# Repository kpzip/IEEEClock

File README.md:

# IEEEClock
Back to the future style clock

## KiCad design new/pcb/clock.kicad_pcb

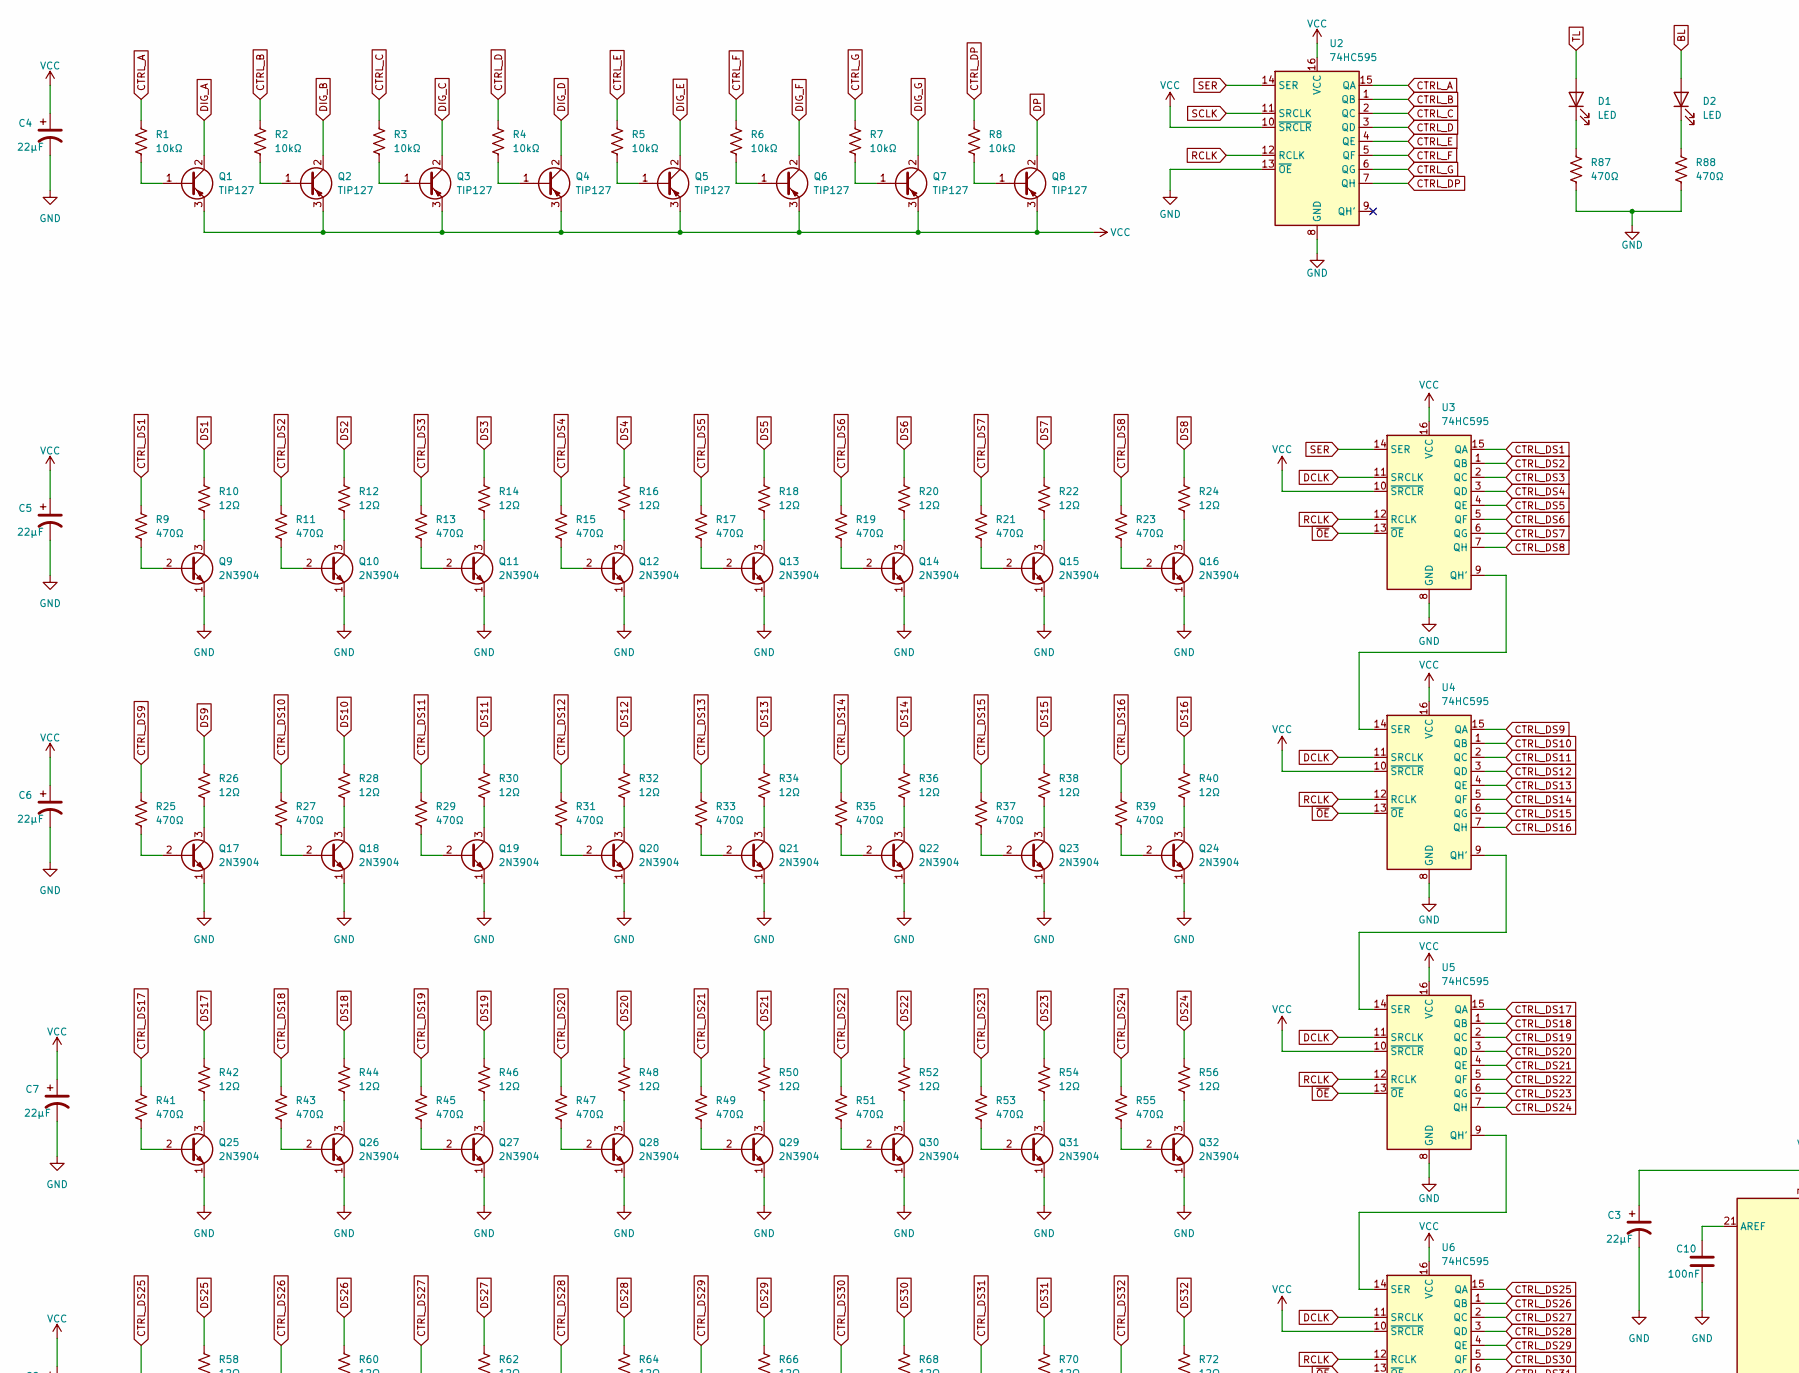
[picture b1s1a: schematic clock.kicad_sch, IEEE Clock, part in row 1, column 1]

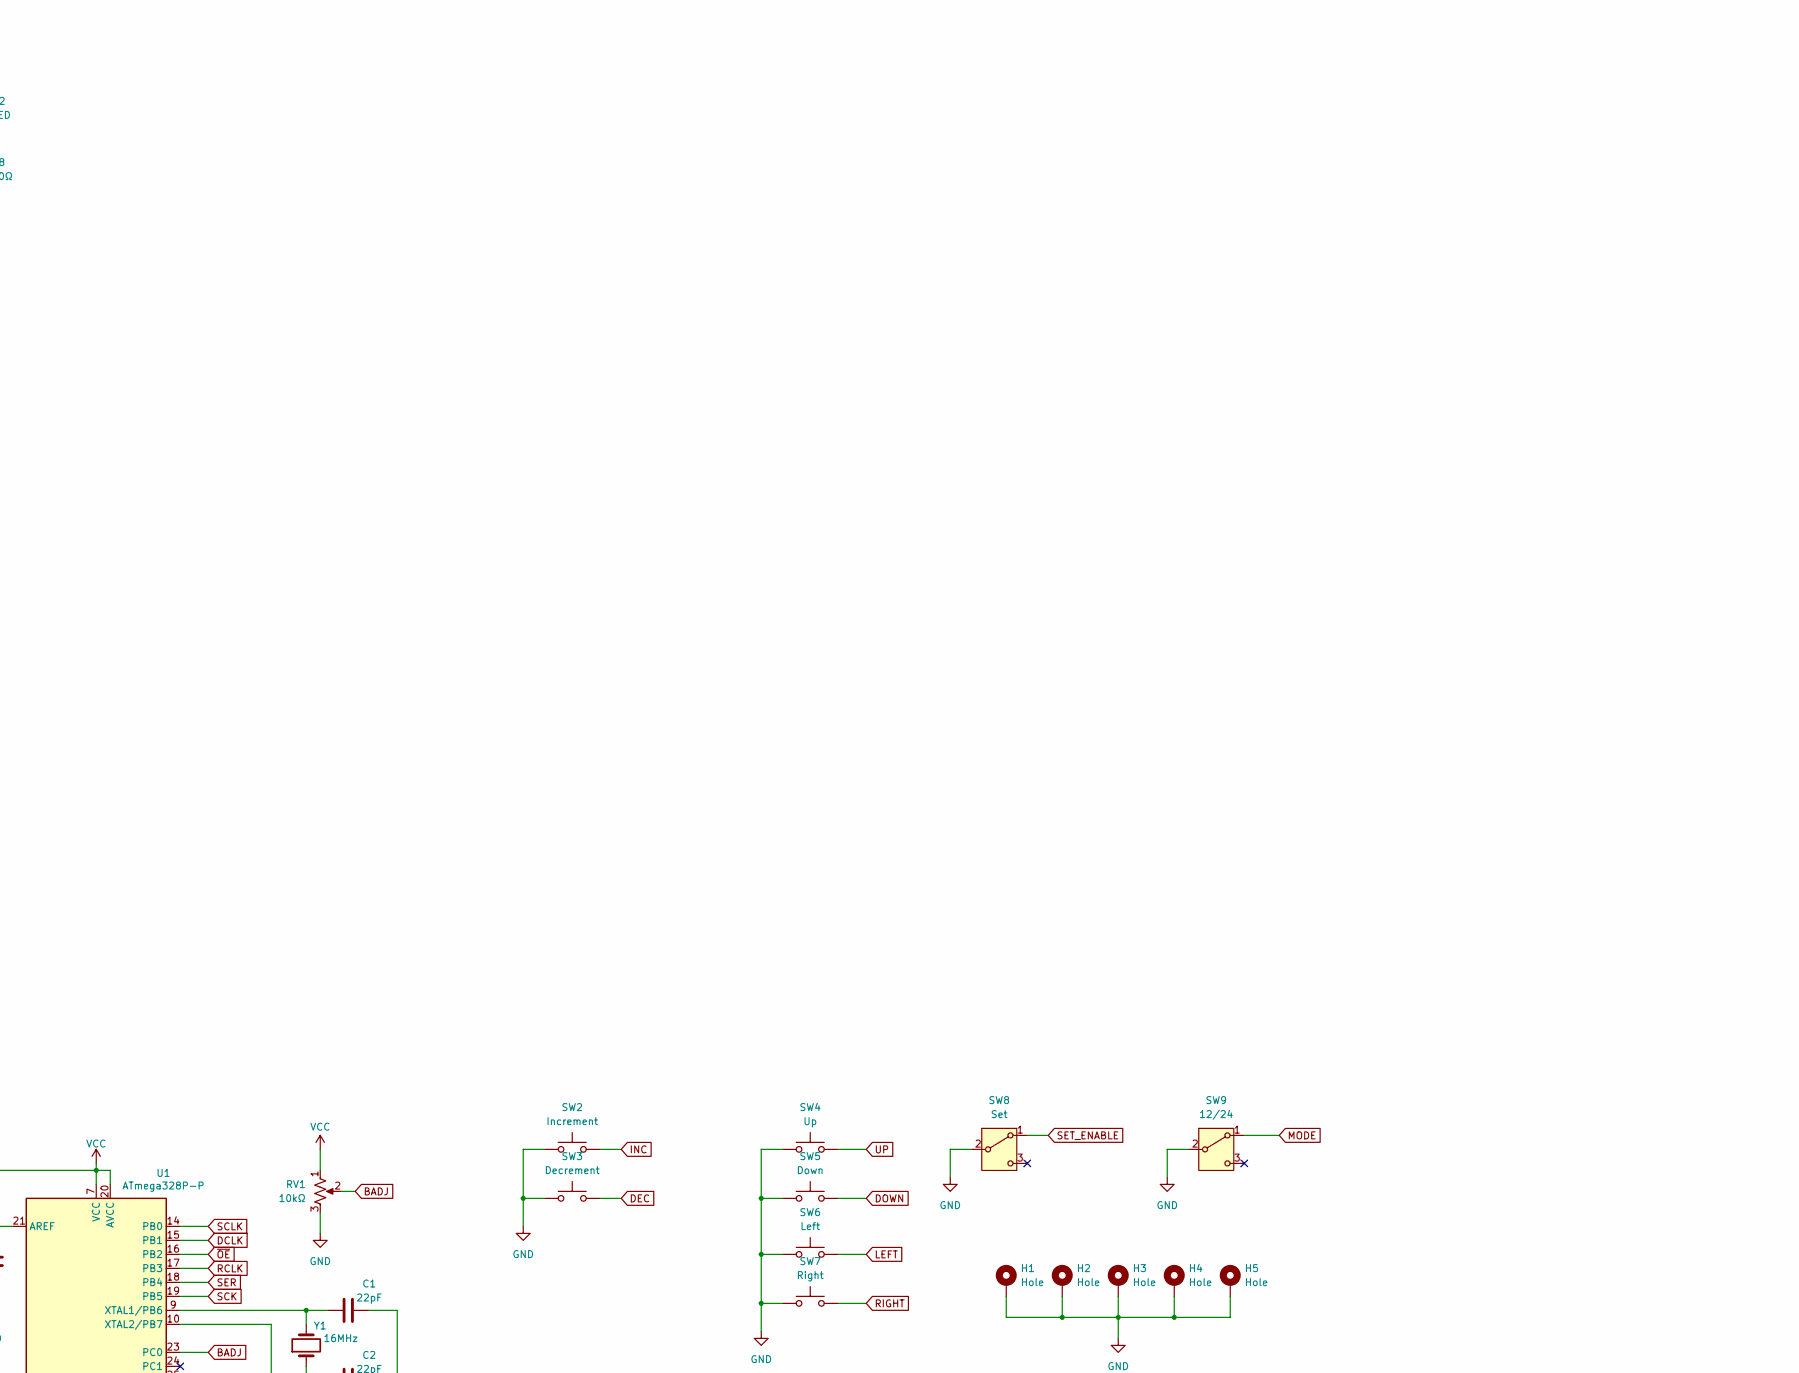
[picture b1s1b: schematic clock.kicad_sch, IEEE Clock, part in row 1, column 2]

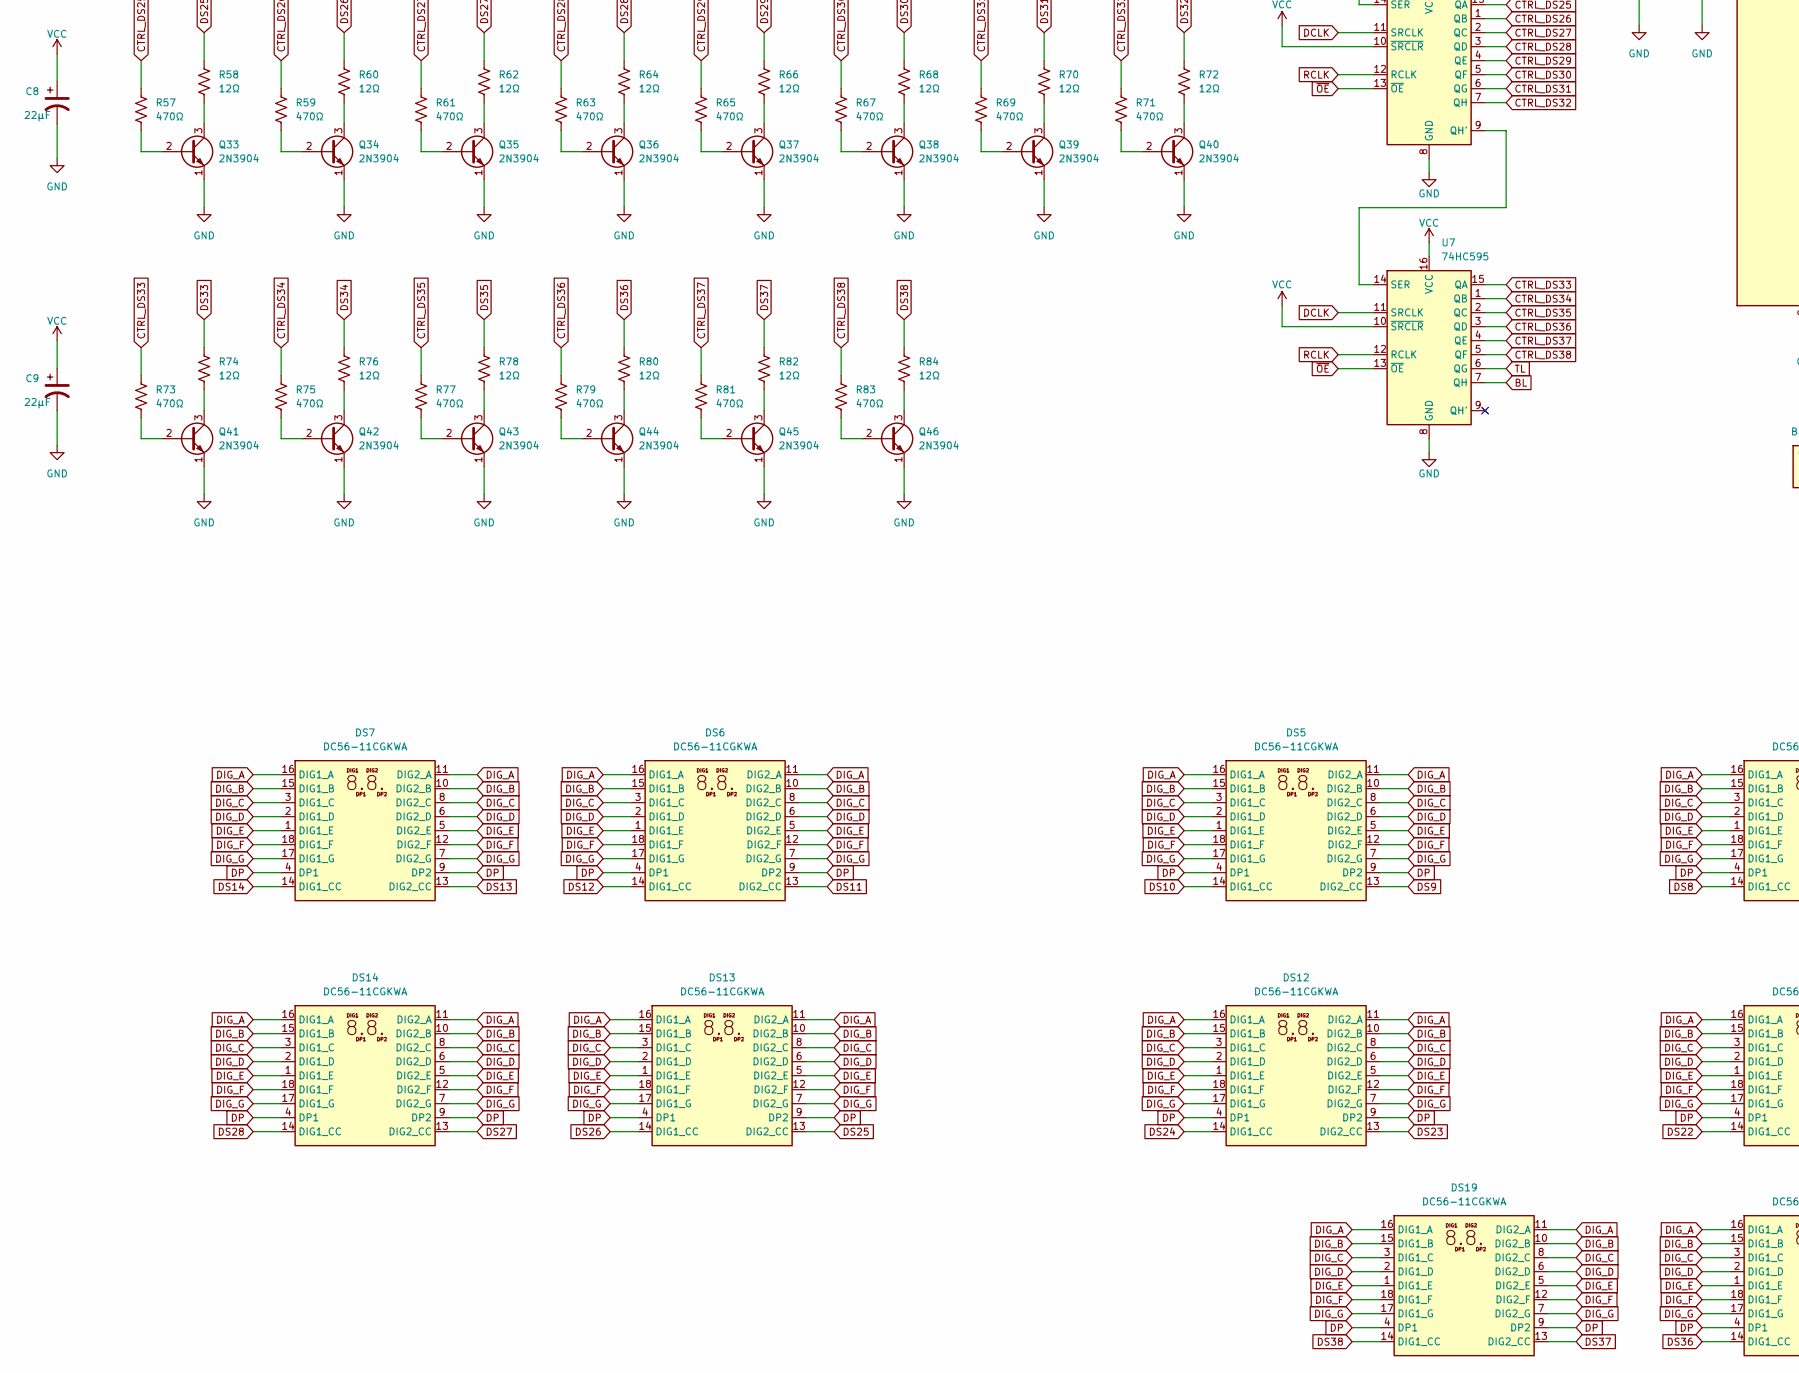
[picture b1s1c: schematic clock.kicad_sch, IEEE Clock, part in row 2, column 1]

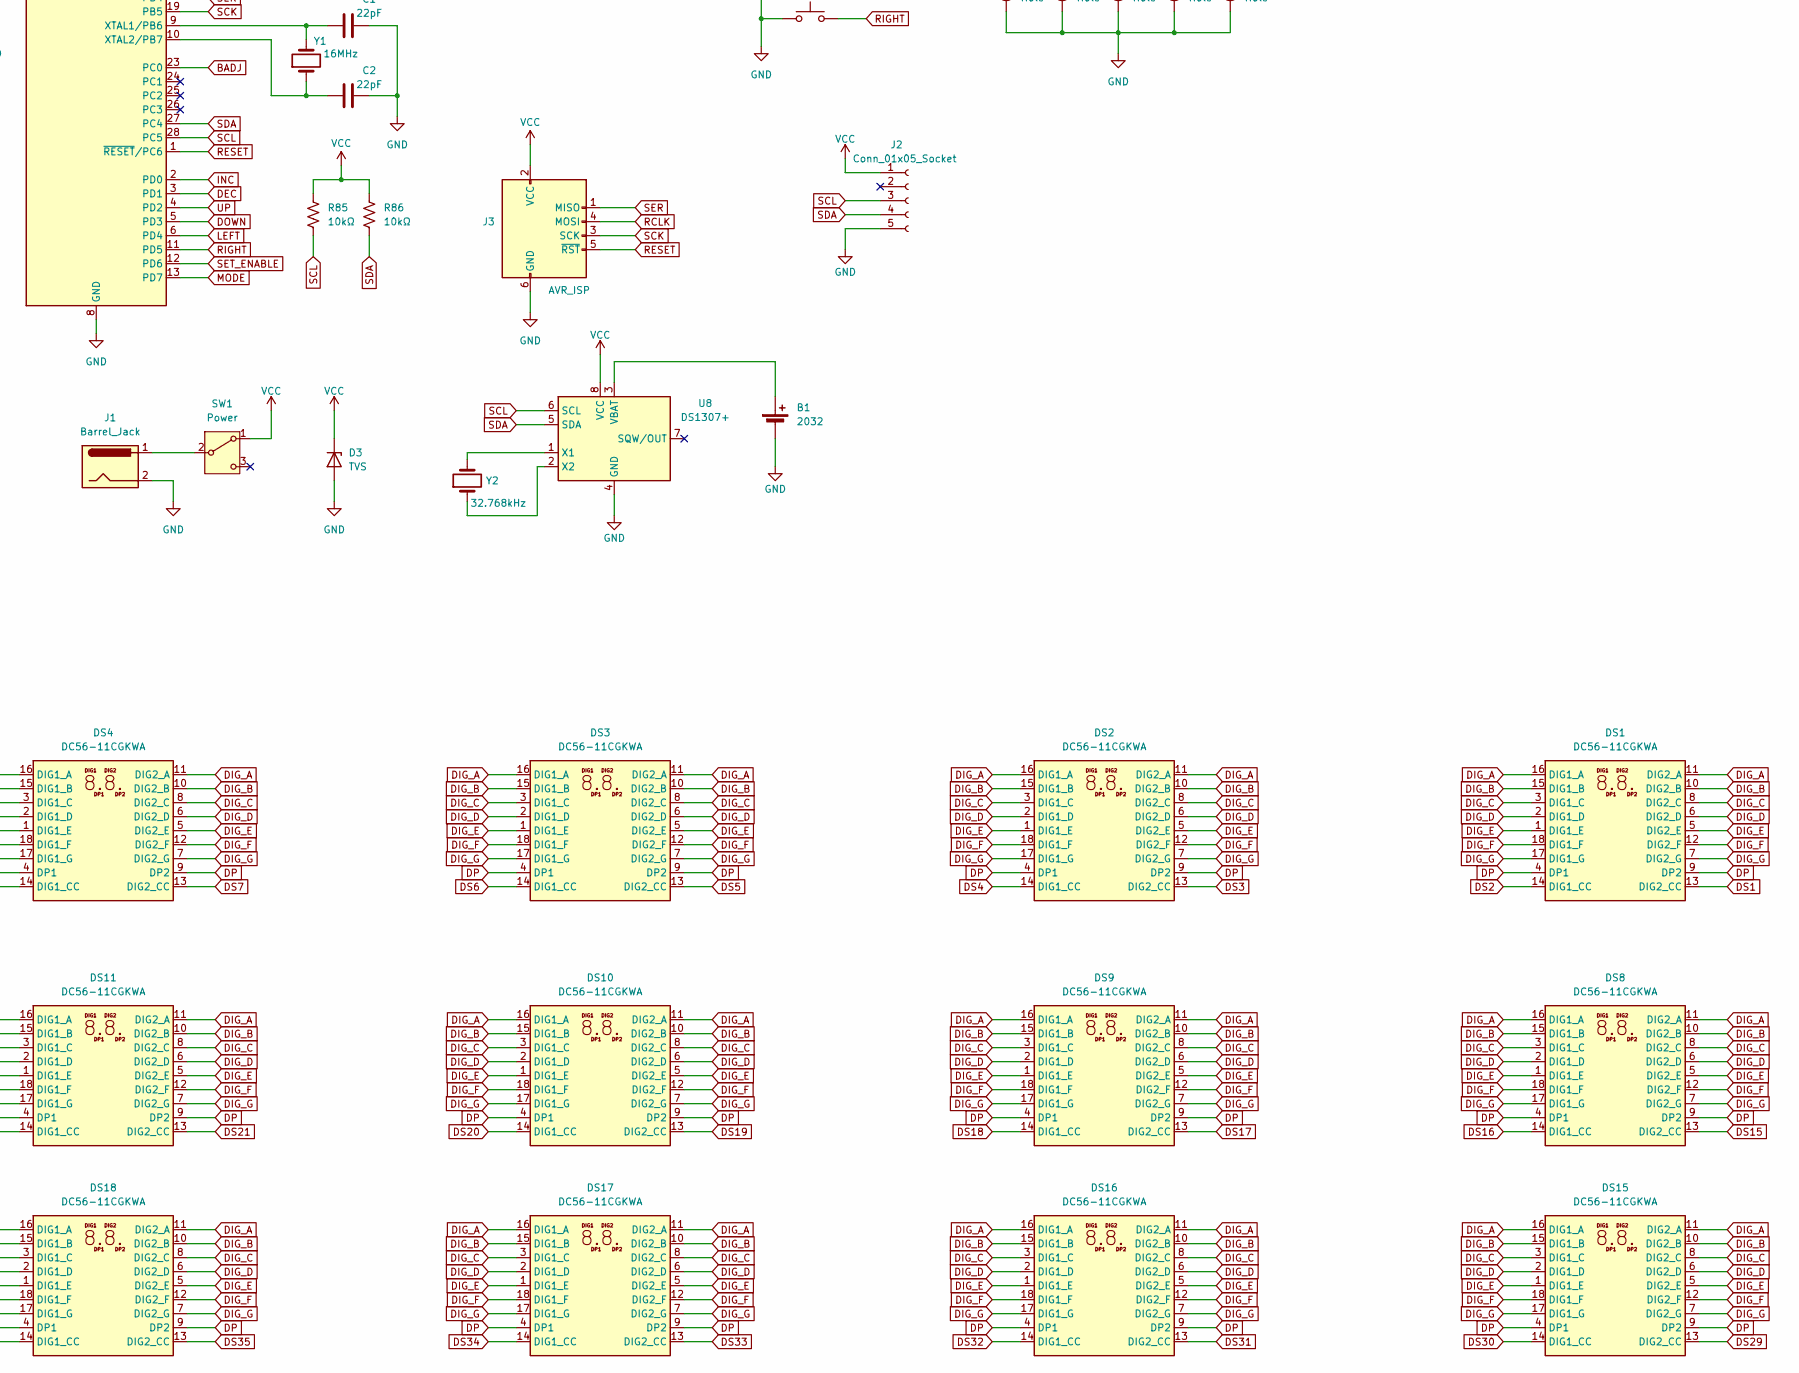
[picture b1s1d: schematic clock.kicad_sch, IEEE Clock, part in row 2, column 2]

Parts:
B1: 2032; BAT_BAT-HLD-001-THM
C1, C2: 22pF; C_1206_3216Metric_Pad1.33x1.80mm_HandSolder
C3, C4, C5, C6, C7, C8, C9: 22μF; CP_Radial_D5.0mm_P2.00mm
C10: 100nF; C_1206_3216Metric_Pad1.33x1.80mm_HandSolder
D1, D2: LED; LED_D5.0mm
D3: TVS; D_SMA_Handsoldering
DS1, DS2, DS3, DS4, DS5, DS6, DS7, DS8, DS9, DS10, DS11, DS12, DS13, DS14, DS15, DS16, DS17, DS18, DS19: DC56-11CGKWA; DIPS2200W51P254L3580H1000Q18N
H1, H2, H3, H4, H5: Hole; MountingHole_2.2mm_M2_ISO7380_Pad
J1: Barrel_Jack; BarrelJack_GCT_DCJ200-10-A_Horizontal
J2: Conn_01x05_Socket; PinSocket_1x05_P2.54mm_Vertical
J3: AVR_ISP; IDC-Header_2x03_P2.54mm_Vertical
Q1, Q2, Q3, Q4, Q5, Q6, Q7, Q8: TIP127; TO-220-3_Horizontal_TabDown
Q9, Q10, Q11, Q12, Q13, Q14, Q15, Q16, Q17, Q18, Q19, Q20, Q21, Q22, Q23, Q24, Q25, Q26, Q27, Q28, Q29, Q30, Q31, Q32, Q33, Q34, Q35, Q36, Q37, Q38, Q39, Q40, Q41, Q42, Q43, Q44, Q45, Q46: 2N3904; TO-92L_Inline
R1, R2, R3, R4, R5, R6, R7, R8, R85, R86: 10kΩ; R_Axial_DIN0207_L6.3mm_D2.5mm_P10.16mm_Horizontal
R9, R11, R13, R15, R17, R19, R21, R23, R25, R27, R29, R31, R33, R35, R37, R39, R41, R43, R45, R47, R49, R51, R53, R55, R57, R59, R61, R63, R65, R67, R69, R71, R73, R75, R77, R79, R81, R83, R87, R88: 470Ω; R_Axial_DIN0207_L6.3mm_D2.5mm_P10.16mm_Horizontal
R10, R12, R14, R16, R18, R20, R22, R24, R26, R28, R30, R32, R34, R36, R38, R40, R42, R44, R46, R48, R50, R52, R54, R56, R58, R60, R62, R64, R66, R68, R70, R72, R74, R76, R78, R80, R82, R84: 12Ω; R_Axial_DIN0207_L6.3mm_D2.5mm_P10.16mm_Horizontal
RV1: 10kΩ; Potentiometer_Bourns_PTV09A-1_Single_Vertical
SW1: Power; SW_Slide-03_Wuerth-WS-SLTV_10x2.5x6.4_P2.54mm
SW2: Increment; SW_PUSH_6mm
SW3: Decrement; SW_PUSH_6mm
SW4: Up; SW_PUSH_6mm
SW5: Down; SW_PUSH_6mm
SW6: Left; SW_PUSH_6mm
SW7: Right; SW_PUSH_6mm
SW8: Set; SW_Slide-03_Wuerth-WS-SLTV_10x2.5x6.4_P2.54mm
SW9: 12/24; SW_Slide-03_Wuerth-WS-SLTV_10x2.5x6.4_P2.54mm
U1: ATmega328P-P; DIP-28_W7.62mm_Socket_LongPads
U2, U3, U4, U5, U6, U7: 74HC595; DIP-16_W7.62mm_Socket_LongPads
U8: DS1307+; DIP-8_W7.62mm_Socket_LongPads
Y1: 16MHz; Crystal_HC49-U_Vertical
Y2: 32.768kHz; Crystal_DS10_D1.0mm_L4.3mm_Vertical

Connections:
BADJ: RV1.2, U1.23 (PC0)
BL: D2.2 (A), U7.7 (QH)
CTRL_A: R1.1, U2.15 (QA)
CTRL_B: R2.1, U2.1 (QB)
CTRL_C: R3.1, U2.2 (QC)
CTRL_D: R4.1, U2.3 (QD)
CTRL_DP: R8.1, U2.7 (QH)
CTRL_DS1: R9.1, U3.15 (QA)
CTRL_DS2: R11.1, U3.1 (QB)
CTRL_DS3: R13.1, U3.2 (QC)
CTRL_DS4: R15.1, U3.3 (QD)
CTRL_DS5: R17.1, U3.4 (QE)
CTRL_DS6: R19.1, U3.5 (QF)
CTRL_DS7: R21.1, U3.6 (QG)
CTRL_DS8: R23.1, U3.7 (QH)
CTRL_DS9: R25.1, U4.15 (QA)
CTRL_DS10: R27.1, U4.1 (QB)
CTRL_DS11: R29.1, U4.2 (QC)
CTRL_DS12: R31.1, U4.3 (QD)
CTRL_DS13: R33.1, U4.4 (QE)
CTRL_DS14: R35.1, U4.5 (QF)
CTRL_DS15: R37.1, U4.6 (QG)
CTRL_DS16: R39.1, U4.7 (QH)
CTRL_DS17: R41.1, U5.15 (QA)
CTRL_DS18: R43.1, U5.1 (QB)
CTRL_DS19: R45.1, U5.2 (QC)
CTRL_DS20: R47.1, U5.3 (QD)
CTRL_DS21: R49.1, U5.4 (QE)
CTRL_DS22: R51.1, U5.5 (QF)
CTRL_DS23: R53.1, U5.6 (QG)
CTRL_DS24: R55.1, U5.7 (QH)
CTRL_DS25: R57.1, U6.15 (QA)
CTRL_DS26: R59.1, U6.1 (QB)
CTRL_DS27: R61.1, U6.2 (QC)
CTRL_DS28: R63.1, U6.3 (QD)
CTRL_DS29: R65.1, U6.4 (QE)
CTRL_DS30: R67.1, U6.5 (QF)
CTRL_DS31: R69.1, U6.6 (QG)
CTRL_DS32: R71.1, U6.7 (QH)
CTRL_DS33: R73.1, U7.15 (QA)
CTRL_DS34: R75.1, U7.1 (QB)
CTRL_DS35: R77.1, U7.2 (QC)
CTRL_DS36: R79.1, U7.3 (QD)
CTRL_DS37: R81.1, U7.4 (QE)
CTRL_DS38: R83.1, U7.5 (QF)
CTRL_E: R5.1, U2.4 (QE)
CTRL_F: R6.1, U2.5 (QF)
CTRL_G: R7.1, U2.6 (QG)
DCLK: U1.15 (PB1), U3.11 (SRCLK), U4.11 (SRCLK), U5.11 (SRCLK), U6.11 (SRCLK), U7.11 (SRCLK)
DEC: SW3.2, U1.3 (PD1)
DIG_A: DS1.11 (DIG2_A), DS1.16 (DIG1_A), DS2.11 (DIG2_A), DS2.16 (DIG1_A), DS3.11 (DIG2_A), DS3.16 (DIG1_A), DS4.11 (DIG2_A), DS4.16 (DIG1_A), DS5.11 (DIG2_A), DS5.16 (DIG1_A), DS6.11 (DIG2_A), DS6.16 (DIG1_A), DS7.11 (DIG2_A), DS7.16 (DIG1_A), DS8.11 (DIG2_A), DS8.16 (DIG1_A), DS9.11 (DIG2_A), DS9.16 (DIG1_A), DS10.11 (DIG2_A), DS10.16 (DIG1_A), DS11.11 (DIG2_A), DS11.16 (DIG1_A), DS12.11 (DIG2_A), DS12.16 (DIG1_A), DS13.11 (DIG2_A), DS13.16 (DIG1_A), DS14.11 (DIG2_A), DS14.16 (DIG1_A), DS15.11 (DIG2_A), DS15.16 (DIG1_A), DS16.11 (DIG2_A), DS16.16 (DIG1_A), DS17.11 (DIG2_A), DS17.16 (DIG1_A), DS18.11 (DIG2_A), DS18.16 (DIG1_A), DS19.11 (DIG2_A), DS19.16 (DIG1_A), Q1.2 (C)
DIG_B: DS1.10 (DIG2_B), DS1.15 (DIG1_B), DS2.10 (DIG2_B), DS2.15 (DIG1_B), DS3.10 (DIG2_B), DS3.15 (DIG1_B), DS4.10 (DIG2_B), DS4.15 (DIG1_B), DS5.10 (DIG2_B), DS5.15 (DIG1_B), DS6.10 (DIG2_B), DS6.15 (DIG1_B), DS7.10 (DIG2_B), DS7.15 (DIG1_B), DS8.10 (DIG2_B), DS8.15 (DIG1_B), DS9.10 (DIG2_B), DS9.15 (DIG1_B), DS10.10 (DIG2_B), DS10.15 (DIG1_B), DS11.10 (DIG2_B), DS11.15 (DIG1_B), DS12.10 (DIG2_B), DS12.15 (DIG1_B), DS13.10 (DIG2_B), DS13.15 (DIG1_B), DS14.10 (DIG2_B), DS14.15 (DIG1_B), DS15.10 (DIG2_B), DS15.15 (DIG1_B), DS16.10 (DIG2_B), DS16.15 (DIG1_B), DS17.10 (DIG2_B), DS17.15 (DIG1_B), DS18.10 (DIG2_B), DS18.15 (DIG1_B), DS19.10 (DIG2_B), DS19.15 (DIG1_B), Q2.2 (C)
DIG_C: DS1.3 (DIG1_C), DS1.8 (DIG2_C), DS2.3 (DIG1_C), DS2.8 (DIG2_C), DS3.3 (DIG1_C), DS3.8 (DIG2_C), DS4.3 (DIG1_C), DS4.8 (DIG2_C), DS5.3 (DIG1_C), DS5.8 (DIG2_C), DS6.3 (DIG1_C), DS6.8 (DIG2_C), DS7.3 (DIG1_C), DS7.8 (DIG2_C), DS8.3 (DIG1_C), DS8.8 (DIG2_C), DS9.3 (DIG1_C), DS9.8 (DIG2_C), DS10.3 (DIG1_C), DS10.8 (DIG2_C), DS11.3 (DIG1_C), DS11.8 (DIG2_C), DS12.3 (DIG1_C), DS12.8 (DIG2_C), DS13.3 (DIG1_C), DS13.8 (DIG2_C), DS14.3 (DIG1_C), DS14.8 (DIG2_C), DS15.3 (DIG1_C), DS15.8 (DIG2_C), DS16.3 (DIG1_C), DS16.8 (DIG2_C), DS17.3 (DIG1_C), DS17.8 (DIG2_C), DS18.3 (DIG1_C), DS18.8 (DIG2_C), DS19.3 (DIG1_C), DS19.8 (DIG2_C), Q3.2 (C)
DIG_D: DS1.2 (DIG1_D), DS1.6 (DIG2_D), DS2.2 (DIG1_D), DS2.6 (DIG2_D), DS3.2 (DIG1_D), DS3.6 (DIG2_D), DS4.2 (DIG1_D), DS4.6 (DIG2_D), DS5.2 (DIG1_D), DS5.6 (DIG2_D), DS6.2 (DIG1_D), DS6.6 (DIG2_D), DS7.2 (DIG1_D), DS7.6 (DIG2_D), DS8.2 (DIG1_D), DS8.6 (DIG2_D), DS9.2 (DIG1_D), DS9.6 (DIG2_D), DS10.2 (DIG1_D), DS10.6 (DIG2_D), DS11.2 (DIG1_D), DS11.6 (DIG2_D), DS12.2 (DIG1_D), DS12.6 (DIG2_D), DS13.2 (DIG1_D), DS13.6 (DIG2_D), DS14.2 (DIG1_D), DS14.6 (DIG2_D), DS15.2 (DIG1_D), DS15.6 (DIG2_D), DS16.2 (DIG1_D), DS16.6 (DIG2_D), DS17.2 (DIG1_D), DS17.6 (DIG2_D), DS18.2 (DIG1_D), DS18.6 (DIG2_D), DS19.2 (DIG1_D), DS19.6 (DIG2_D), Q4.2 (C)
DIG_E: DS1.1 (DIG1_E), DS1.5 (DIG2_E), DS2.1 (DIG1_E), DS2.5 (DIG2_E), DS3.1 (DIG1_E), DS3.5 (DIG2_E), DS4.1 (DIG1_E), DS4.5 (DIG2_E), DS5.1 (DIG1_E), DS5.5 (DIG2_E), DS6.1 (DIG1_E), DS6.5 (DIG2_E), DS7.1 (DIG1_E), DS7.5 (DIG2_E), DS8.1 (DIG1_E), DS8.5 (DIG2_E), DS9.1 (DIG1_E), DS9.5 (DIG2_E), DS10.1 (DIG1_E), DS10.5 (DIG2_E), DS11.1 (DIG1_E), DS11.5 (DIG2_E), DS12.1 (DIG1_E), DS12.5 (DIG2_E), DS13.1 (DIG1_E), DS13.5 (DIG2_E), DS14.1 (DIG1_E), DS14.5 (DIG2_E), DS15.1 (DIG1_E), DS15.5 (DIG2_E), DS16.1 (DIG1_E), DS16.5 (DIG2_E), DS17.1 (DIG1_E), DS17.5 (DIG2_E), DS18.1 (DIG1_E), DS18.5 (DIG2_E), DS19.1 (DIG1_E), DS19.5 (DIG2_E), Q5.2 (C)
DIG_F: DS1.12 (DIG2_F), DS1.18 (DIG1_F), DS2.12 (DIG2_F), DS2.18 (DIG1_F), DS3.12 (DIG2_F), DS3.18 (DIG1_F), DS4.12 (DIG2_F), DS4.18 (DIG1_F), DS5.12 (DIG2_F), DS5.18 (DIG1_F), DS6.12 (DIG2_F), DS6.18 (DIG1_F), DS7.12 (DIG2_F), DS7.18 (DIG1_F), DS8.12 (DIG2_F), DS8.18 (DIG1_F), DS9.12 (DIG2_F), DS9.18 (DIG1_F), DS10.12 (DIG2_F), DS10.18 (DIG1_F), DS11.12 (DIG2_F), DS11.18 (DIG1_F), DS12.12 (DIG2_F), DS12.18 (DIG1_F), DS13.12 (DIG2_F), DS13.18 (DIG1_F), DS14.12 (DIG2_F), DS14.18 (DIG1_F), DS15.12 (DIG2_F), DS15.18 (DIG1_F), DS16.12 (DIG2_F), DS16.18 (DIG1_F), DS17.12 (DIG2_F), DS17.18 (DIG1_F), DS18.12 (DIG2_F), DS18.18 (DIG1_F), DS19.12 (DIG2_F), DS19.18 (DIG1_F), Q6.2 (C)
DIG_G: DS1.7 (DIG2_G), DS1.17 (DIG1_G), DS2.7 (DIG2_G), DS2.17 (DIG1_G), DS3.7 (DIG2_G), DS3.17 (DIG1_G), DS4.7 (DIG2_G), DS4.17 (DIG1_G), DS5.7 (DIG2_G), DS5.17 (DIG1_G), DS6.7 (DIG2_G), DS6.17 (DIG1_G), DS7.7 (DIG2_G), DS7.17 (DIG1_G), DS8.7 (DIG2_G), DS8.17 (DIG1_G), DS9.7 (DIG2_G), DS9.17 (DIG1_G), DS10.7 (DIG2_G), DS10.17 (DIG1_G), DS11.7 (DIG2_G), DS11.17 (DIG1_G), DS12.7 (DIG2_G), DS12.17 (DIG1_G), DS13.7 (DIG2_G), DS13.17 (DIG1_G), DS14.7 (DIG2_G), DS14.17 (DIG1_G), DS15.7 (DIG2_G), DS15.17 (DIG1_G), DS16.7 (DIG2_G), DS16.17 (DIG1_G), DS17.7 (DIG2_G), DS17.17 (DIG1_G), DS18.7 (DIG2_G), DS18.17 (DIG1_G), DS19.7 (DIG2_G), DS19.17 (DIG1_G), Q7.2 (C)
DOWN: SW5.2, U1.5 (PD3)
DP: DS1.4 (DP1), DS1.9 (DP2), DS2.4 (DP1), DS2.9 (DP2), DS3.4 (DP1), DS3.9 (DP2), DS4.4 (DP1), DS4.9 (DP2), DS5.4 (DP1), DS5.9 (DP2), DS6.4 (DP1), DS6.9 (DP2), DS7.4 (DP1), DS7.9 (DP2), DS8.4 (DP1), DS8.9 (DP2), DS9.4 (DP1), DS9.9 (DP2), DS10.4 (DP1), DS10.9 (DP2), DS11.4 (DP1), DS11.9 (DP2), DS12.4 (DP1), DS12.9 (DP2), DS13.4 (DP1), DS13.9 (DP2), DS14.4 (DP1), DS14.9 (DP2), DS15.4 (DP1), DS15.9 (DP2), DS16.4 (DP1), DS16.9 (DP2), DS17.4 (DP1), DS17.9 (DP2), DS18.4 (DP1), DS18.9 (DP2), DS19.4 (DP1), DS19.9 (DP2), Q8.2 (C)
DS1: DS1.13 (DIG2_CC), R10.1
DS2: DS1.14 (DIG1_CC), R12.1
DS3: DS2.13 (DIG2_CC), R14.1
DS4: DS2.14 (DIG1_CC), R16.1
DS5: DS3.13 (DIG2_CC), R18.1
DS6: DS3.14 (DIG1_CC), R20.1
DS7: DS4.13 (DIG2_CC), R22.1
DS8: DS4.14 (DIG1_CC), R24.1
DS9: DS5.13 (DIG2_CC), R26.1
DS10: DS5.14 (DIG1_CC), R28.1
DS11: DS6.13 (DIG2_CC), R30.1
DS12: DS6.14 (DIG1_CC), R32.1
DS13: DS7.13 (DIG2_CC), R34.1
DS14: DS7.14 (DIG1_CC), R36.1
DS15: DS8.13 (DIG2_CC), R38.1
DS16: DS8.14 (DIG1_CC), R40.1
DS17: DS9.13 (DIG2_CC), R42.1
DS18: DS9.14 (DIG1_CC), R44.1
DS19: DS10.13 (DIG2_CC), R46.1
DS20: DS10.14 (DIG1_CC), R48.1
DS21: DS11.13 (DIG2_CC), R50.1
DS22: DS11.14 (DIG1_CC), R52.1
DS23: DS12.13 (DIG2_CC), R54.1
DS24: DS12.14 (DIG1_CC), R56.1
DS25: DS13.13 (DIG2_CC), R58.1
DS26: DS13.14 (DIG1_CC), R60.1
DS27: DS14.13 (DIG2_CC), R62.1
DS28: DS14.14 (DIG1_CC), R64.1
DS29: DS15.13 (DIG2_CC), R66.1
DS30: DS15.14 (DIG1_CC), R68.1
DS31: DS16.13 (DIG2_CC), R70.1
DS32: DS16.14 (DIG1_CC), R72.1
DS33: DS17.13 (DIG2_CC), R74.1
DS34: DS17.14 (DIG1_CC), R76.1
DS35: DS18.13 (DIG2_CC), R78.1
DS36: DS18.14 (DIG1_CC), R80.1
DS37: DS19.13 (DIG2_CC), R82.1
DS38: DS19.14 (DIG1_CC), R84.1
GND: B1.2 (-), C1.2, C2.2, C3.2, C4.2, C5.2, C6.2, C7.2, C8.2, C9.2, C10.2, D3.2 (A), H1.1, H2.1, H3.1, H4.1, H5.1, J1.2, J2.5, J3.6 (GND), Q9.1 (E), Q10.1 (E), Q11.1 (E), Q12.1 (E), Q13.1 (E), Q14.1 (E), Q15.1 (E), Q16.1 (E), Q17.1 (E), Q18.1 (E), Q19.1 (E), Q20.1 (E), Q21.1 (E), Q22.1 (E), Q23.1 (E), Q24.1 (E), Q25.1 (E), Q26.1 (E), Q27.1 (E), Q28.1 (E), Q29.1 (E), Q30.1 (E), Q31.1 (E), Q32.1 (E), Q33.1 (E), Q34.1 (E), Q35.1 (E), Q36.1 (E), Q37.1 (E), Q38.1 (E), Q39.1 (E), Q40.1 (E), Q41.1 (E), Q42.1 (E), Q43.1 (E), Q44.1 (E), Q45.1 (E), Q46.1 (E), R87.2, R88.2, RV1.3, SW2.1, SW3.1, SW4.1, SW5.1, SW6.1, SW7.1, SW8.2 (B), SW9.2 (B), U1.8 (GND), U1.22 (GND), U2.8 (GND), U2.13 (~OE), U3.8 (GND), U4.8 (GND), U5.8 (GND), U6.8 (GND), U7.8 (GND), U8.4 (GND)
INC: SW2.2, U1.2 (PD0)
LEFT: SW6.2, U1.6 (PD4)
MODE: SW9.1 (A), U1.13 (PD7)
unnamed: B1.1 (+), U8.3 (VBAT)
unnamed: D1.1 (K), R87.1
unnamed: D2.1 (K), R88.1
unnamed: Q1.1 (B), R1.2
unnamed: Q2.1 (B), R2.2
unnamed: Q3.1 (B), R3.2
unnamed: Q4.1 (B), R4.2
unnamed: Q5.1 (B), R5.2
unnamed: Q6.1 (B), R6.2
unnamed: Q7.1 (B), R7.2
unnamed: Q8.1 (B), R8.2
unnamed: Q9.2 (B), R9.2
unnamed: Q9.3 (C), R10.2
unnamed: Q10.2 (B), R11.2
unnamed: Q10.3 (C), R12.2
unnamed: Q11.2 (B), R13.2
unnamed: Q11.3 (C), R14.2
unnamed: Q12.2 (B), R15.2
unnamed: Q12.3 (C), R16.2
unnamed: Q13.2 (B), R17.2
unnamed: Q13.3 (C), R18.2
unnamed: Q14.2 (B), R19.2
unnamed: Q14.3 (C), R20.2
unnamed: Q15.2 (B), R21.2
unnamed: Q15.3 (C), R22.2
unnamed: Q16.2 (B), R23.2
unnamed: Q16.3 (C), R24.2
unnamed: Q17.2 (B), R25.2
unnamed: Q17.3 (C), R26.2
unnamed: Q18.2 (B), R27.2
unnamed: Q18.3 (C), R28.2
unnamed: Q19.2 (B), R29.2
unnamed: Q19.3 (C), R30.2
unnamed: Q20.2 (B), R31.2
unnamed: Q20.3 (C), R32.2
unnamed: Q21.2 (B), R33.2
unnamed: Q21.3 (C), R34.2
unnamed: Q22.2 (B), R35.2
unnamed: Q22.3 (C), R36.2
unnamed: Q23.2 (B), R37.2
unnamed: Q23.3 (C), R38.2
unnamed: Q24.2 (B), R39.2
unnamed: Q24.3 (C), R40.2
unnamed: Q25.2 (B), R41.2
unnamed: Q25.3 (C), R42.2
unnamed: Q26.2 (B), R43.2
unnamed: Q26.3 (C), R44.2
unnamed: Q27.2 (B), R45.2
unnamed: Q27.3 (C), R46.2
unnamed: Q28.2 (B), R47.2
unnamed: Q28.3 (C), R48.2
unnamed: Q29.2 (B), R49.2
unnamed: Q29.3 (C), R50.2
unnamed: Q30.2 (B), R51.2
unnamed: Q30.3 (C), R52.2
unnamed: Q31.2 (B), R53.2
unnamed: Q31.3 (C), R54.2
unnamed: Q32.2 (B), R55.2
unnamed: Q32.3 (C), R56.2
unnamed: Q33.2 (B), R57.2
unnamed: Q33.3 (C), R58.2
unnamed: Q34.2 (B), R59.2
unnamed: Q34.3 (C), R60.2
unnamed: Q35.2 (B), R61.2
unnamed: Q35.3 (C), R62.2
unnamed: Q36.2 (B), R63.2
unnamed: Q36.3 (C), R64.2
unnamed: Q37.2 (B), R65.2
unnamed: Q37.3 (C), R66.2
unnamed: Q38.2 (B), R67.2
unnamed: Q38.3 (C), R68.2
unnamed: Q39.2 (B), R69.2
unnamed: Q39.3 (C), R70.2
unnamed: Q40.2 (B), R71.2
unnamed: Q40.3 (C), R72.2
unnamed: Q41.2 (B), R73.2
unnamed: Q41.3 (C), R74.2
unnamed: Q42.2 (B), R75.2
unnamed: Q42.3 (C), R76.2
unnamed: Q43.2 (B), R77.2
unnamed: Q43.3 (C), R78.2
unnamed: Q44.2 (B), R79.2
unnamed: Q44.3 (C), R80.2
unnamed: Q45.2 (B), R81.2
unnamed: Q45.3 (C), R82.2
unnamed: Q46.2 (B), R83.2
unnamed: Q46.3 (C), R84.2
unnamed: J1.1, SW1.2 (B)
unnamed: C10.1, U1.21 (AREF)
unnamed: C1.1, U1.9 (XTAL1/PB6), Y1.2
unnamed: C2.1, U1.10 (XTAL2/PB7), Y1.1
unnamed: U3.9 (QH'), U4.14 (SER)
unnamed: U4.9 (QH'), U5.14 (SER)
unnamed: U5.9 (QH'), U6.14 (SER)
unnamed: U6.9 (QH'), U7.14 (SER)
unnamed: U8.1 (X1), Y2.2
unnamed: U8.2 (X2), Y2.1
RCLK: J3.4 (MOSI), U1.17 (PB3), U2.12 (RCLK), U3.12 (RCLK), U4.12 (RCLK), U5.12 (RCLK), U6.12 (RCLK), U7.12 (RCLK)
RESET: J3.5 (~RST), U1.1 (~RESET/PC6)
RIGHT: SW7.2, U1.11 (PD5)
SCK: J3.3 (SCK), U1.19 (PB5)
SCL: J2.3, R85.2, U1.28 (PC5), U8.6 (SCL)
SCLK: U1.14 (PB0), U2.11 (SRCLK)
SDA: J2.4, R86.2, U1.27 (PC4), U8.5 (SDA)
SER: J3.1 (MISO), U1.18 (PB4), U2.14 (SER), U3.14 (SER)
SET_ENABLE: SW8.1 (A), U1.12 (PD6)
TL: D1.2 (A), U7.6 (QG)
UP: SW4.2, U1.4 (PD2)
VCC: C3.1, C4.1, C5.1, C6.1, C7.1, C8.1, C9.1, D3.1 (K), J2.1, J3.2 (VCC), Q1.3 (E), Q2.3 (E), Q3.3 (E), Q4.3 (E), Q5.3 (E), Q6.3 (E), Q7.3 (E), Q8.3 (E), R85.1, R86.1, RV1.1, SW1.1 (A), U1.7 (VCC), U1.20 (AVCC), U2.10 (~SRCLR), U2.16 (VCC), U3.10 (~SRCLR), U3.16 (VCC), U4.10 (~SRCLR), U4.16 (VCC), U5.10 (~SRCLR), U5.16 (VCC), U6.10 (~SRCLR), U6.16 (VCC), U7.10 (~SRCLR), U7.16 (VCC), U8.8 (VCC)
~OE: U1.16 (PB2), U3.13 (~OE), U4.13 (~OE), U5.13 (~OE), U6.13 (~OE), U7.13 (~OE)

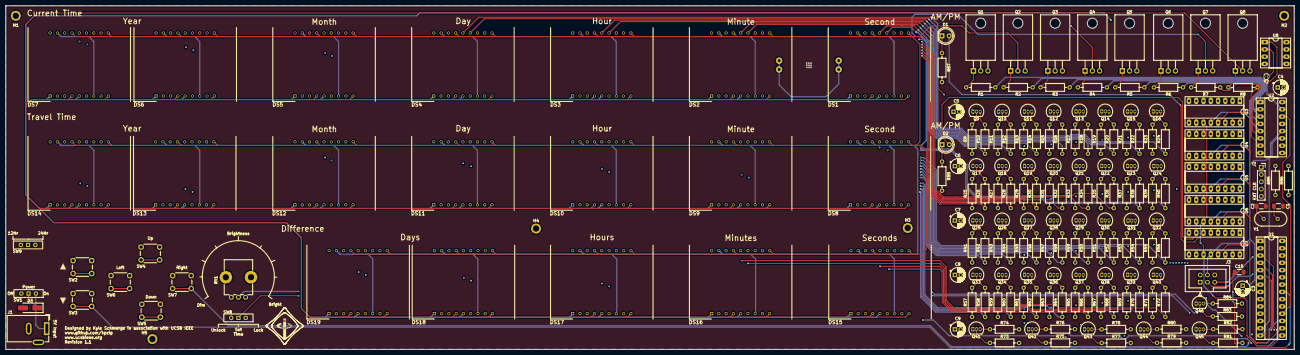
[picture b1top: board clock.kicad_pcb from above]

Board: 4 copper layers, 450.0 x 120.0 mm, 196 parts (1 on the bottom side), 211 nets.

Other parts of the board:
LG1: Logo_Open_Hardware_Small; UCSB_IEEE_Logo

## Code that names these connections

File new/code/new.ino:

#include <Wire.h>
#include <RTClib.h>
#include <EEPROM.h>

// Constants
#define TOP_LEN 14
#define BOTTOM_LEN 14
#define DIFF_LEN 10

#define SHIFT_DELAY_US 1

// Settings
#define USE_FULLER_6
#define LEADING_ZEROS

// Pin numbers
#define SEGMENT_CLK 8
#define DIGIT_CLK 9
#define OUTPUT_ENABLE 10
#define PUSH 11
#define SERIAL_DATA 12

#define INC 0
#define DEC 1
#define UP 2
#define DOWN 3
#define LEFT 4
#define RIGHT 5
#define SET_ENABLE 6
#define MODE 7

#define BRIGHTNESS_ADJ PIN_A0

// Values
// You would think i'm the secretary of state with how much state this simple clock has
const volatile DateTime compile_time(__DATE__, __TIME__);
static volatile DateTime now;
static volatile DateTime travel_time = compile_time;
static volatile TimeSpan difference;

static volatile char top_line[TOP_LEN + 1] = { ' ' };
static volatile char bottom_line[BOTTOM_LEN + 1] = { ' ' };
static volatile char diff_line[DIFF_LEN + 1] = { ' ' };

// State
static volatile bool is_setting_time = false;
static volatile bool is_12_hr = false;
// 0 is top row, 1 is middle row, 2 is difference row
static volatile uint8_t cursor_row = 0;
// 0 is rightmost side
static volatile uint8_t cursor_column = 0;

static volatile bool inc_is_pressed = false;
static volatile bool inc_press_handled = false;
static volatile int inc_pressed_time = 0;

static volatile bool dec_is_pressed = false;
static volatile bool dec_press_handled = false;
static volatile int dec_pressed_time = 0;

static volatile bool up_is_pressed = false;
static volatile bool up_press_handled = false;
static volatile int up_pressed_time = 0;

static volatile bool down_is_pressed = false;
static volatile bool down_press_handled = false;
static volatile int down_pressed_time = 0;

static volatile bool left_is_pressed = false;
static volatile bool left_press_handled = false;
static volatile int left_pressed_time = 0;

static volatile bool right_is_pressed = false;
static volatile bool right_press_handled = false;
static volatile int right_pressed_time = 0;

static volatile RTC_DS1307 rtc; // DS1307 I2C address

void write_date_to_eeprom(DateTime date) {
  // TODO Redundancy
  EEPROM.put <uint32_t> (0, date.unixtime());
}

DateTime read_date_from_eeprom() {
  uint32_t utime;
  EEPROM.get <uint32_t> (0, utime);
  if (utime == 0) {
    return DateTime(compile_time);
  }
  return DateTime(utime);
}

void setup() {
  Serial.begin(9600);

  // Clock Data Pins
  pinMode(SEGMENT_CLK, OUTPUT);
  pinMode(DIGIT_CLK, OUTPUT);
  pinMode(OUTPUT_ENABLE, OUTPUT);
  pinMode(PUSH, OUTPUT);
  pinMode(SERIAL_DATA, OUTPUT);

  // Settings pins
  pinMode(INC, INPUT_PULLUP);
  pinMode(DEC, INPUT_PULLUP);
  pinMode(UP, INPUT_PULLUP);
  pinMode(DOWN, INPUT_PULLUP);
  pinMode(LEFT, INPUT_PULLUP);
  pinMode(RIGHT, INPUT_PULLUP);
  pinMode(SET_ENABLE, INPUT_PULLUP);
  pinMode(MODE, INPUT_PULLUP);

  digitalWrite(SEGMENT_CLK, LOW);
  digitalWrite(DIGIT_CLK, LOW);
  //digitalWrite(OUTPUT_ENABLE, HIGH);
  digitalWrite(PUSH, LOW);
  digitalWrite(SERIAL_DATA, LOW);

  auto second_time = travel_time;

  uint16_t bottom_year = second_time.year();
  uint8_t bottom_month = second_time.month();
  uint8_t bottom_day = second_time.day();
  uint8_t bottom_hour = second_time.hour();
  uint8_t bottom_minute = second_time.minute();
  uint8_t bottom_second = second_time.second();

  while (!Serial) {
    ; // Wait for serial port to connect (for safety)
  }
  if(!rtc.begin()) {
    Serial.println("Couldn't find RTC");
    Serial.flush();
    abort();
  }

  // Init
  now = rtc.now();
  difference = now - compile_time;

  // Read the set time from EEPROM. If it is not set, this function returns the compile time
  travel_time = read_date_from_eeprom();

  // Uncomment the following lines to set the time and date
  //rtc.adjust(compile_time);
}

const bool ZERO_SEGMENTS[7] PROGMEM = {true, true, true, true, true, true, false};
const bool ONE_SEGMENTS[7] PROGMEM = {false, true, true, false, false, false, false};
const bool TWO_SEGMENTS[7] PROGMEM = {true, true, false, true, true, false, true};
const bool THREE_SEGMENTS[7] PROGMEM = {true, true, true, true, false, false, true};
const bool FOUR_SEGMENTS[7] PROGMEM = {false, true, true, false, false, true, true};
const bool FIVE_SEGMENTS[7] PROGMEM = {true, false, true, true, false, true, true};
const bool SIX_SEGMENTS[7] PROGMEM = {false, false, true, true, true, true, true};
const bool SEVEN_SEGMENTS[7] PROGMEM = {true, true, true, false, false, false, false};
const bool EIGHT_SEGMENTS[7] PROGMEM = {true, true, true, true, true, true, true};
const bool NINE_SEGMENTS[7] PROGMEM = {true, true, true, false, false, true, true};

bool c_has_segment(char c, char index) {

  if (index >= 7) {
    return false;
  }

  if (c == ' ' || c < 48) {
    return false;
  }
  // ASCII offset
  uint8_t digit = c - 48;
  // Put these all in one array maybe?
  switch(digit) {
  case 0:
    return ZERO_SEGMENTS[index];
  case 1:
    return ONE_SEGMENTS[index];
  case 2:
    return TWO_SEGMENTS[index];
  case 3:
    return THREE_SEGMENTS[index];
  case 4:
    return FOUR_SEGMENTS[index];
  case 5:
    return FIVE_SEGMENTS[index];
  case 6:
    return SIX_SEGMENTS[index];
  case 7:
    return SEVEN_SEGMENTS[index];
  case 8:
    return EIGHT_SEGMENTS[index];
  case 9:
    return NINE_SEGMENTS[index];
  }
  return false;
}

void loop() {
  // Read in pin data
  int brightness = 1023 - analogRead(BRIGHTNESS_ADJ);
  analogWrite(OUTPUT_ENABLE, brightness/4);

  inc_is_pressed = digitalRead(INC) == LOW;
  dec_is_pressed = digitalRead(DEC) == LOW;
  up_is_pressed = digitalRead(UP) == LOW;
  down_is_pressed = digitalRead(DOWN) == LOW;
  left_is_pressed = digitalRead(LEFT) == LOW;
  right_is_pressed = digitalRead(RIGHT) == LOW;

  is_setting_time = digitalRead(SET_ENABLE) == HIGH;
  is_12_hr = digitalRead(MODE) == LOW;


}

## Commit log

2025-05-01 rtc usage
2025-05-02 ignore kicad
2025-05-02 work
2025-05-03 restructure
2025-05-03 old schematic
2025-05-06 huge
2025-05-06 almost
2025-05-07 done?
2025-05-08 holes
2025-05-08 revision number
2025-05-20 avr isp
2025-05-29 archive 1.0 + fixes
2025-05-30 run it back
2025-06-01 rename
2025-06-02 Re add fixes
2025-06-02 use pwm again
2025-06-02 set title
2025-06-02 logo
2025-06-03 fix firmware
2025-06-03 archive
2025-07-02 eeprom
2025-07-20 afplghjh
2025-07-27 so close yet so far
2025-08-11 hello if you are reading this
